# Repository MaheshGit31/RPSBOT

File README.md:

# RPSBOT

A rock-paper-scissors machine built with no microcontroller and, no firmware.

## Parts List

**4 BUTTONS**

**1. Clock — NE555 (U1)**

**2. Counter — CD4017 (U2)**

**3. Latches — 74HC02 NOR gates (U3, U4)**

**4. Comparator — 74HC08 AND + 74HC32 OR (U5–U9)**

(P = your pick, C = the computer's pick, r/p/s = rock/paper/scissors)

## Files

- `rps_logic.kicad_sch` / `rps_logic.kicad_pro` — schematic
- `rps_logic.kicad_pcb` — routed PCB 

## Images

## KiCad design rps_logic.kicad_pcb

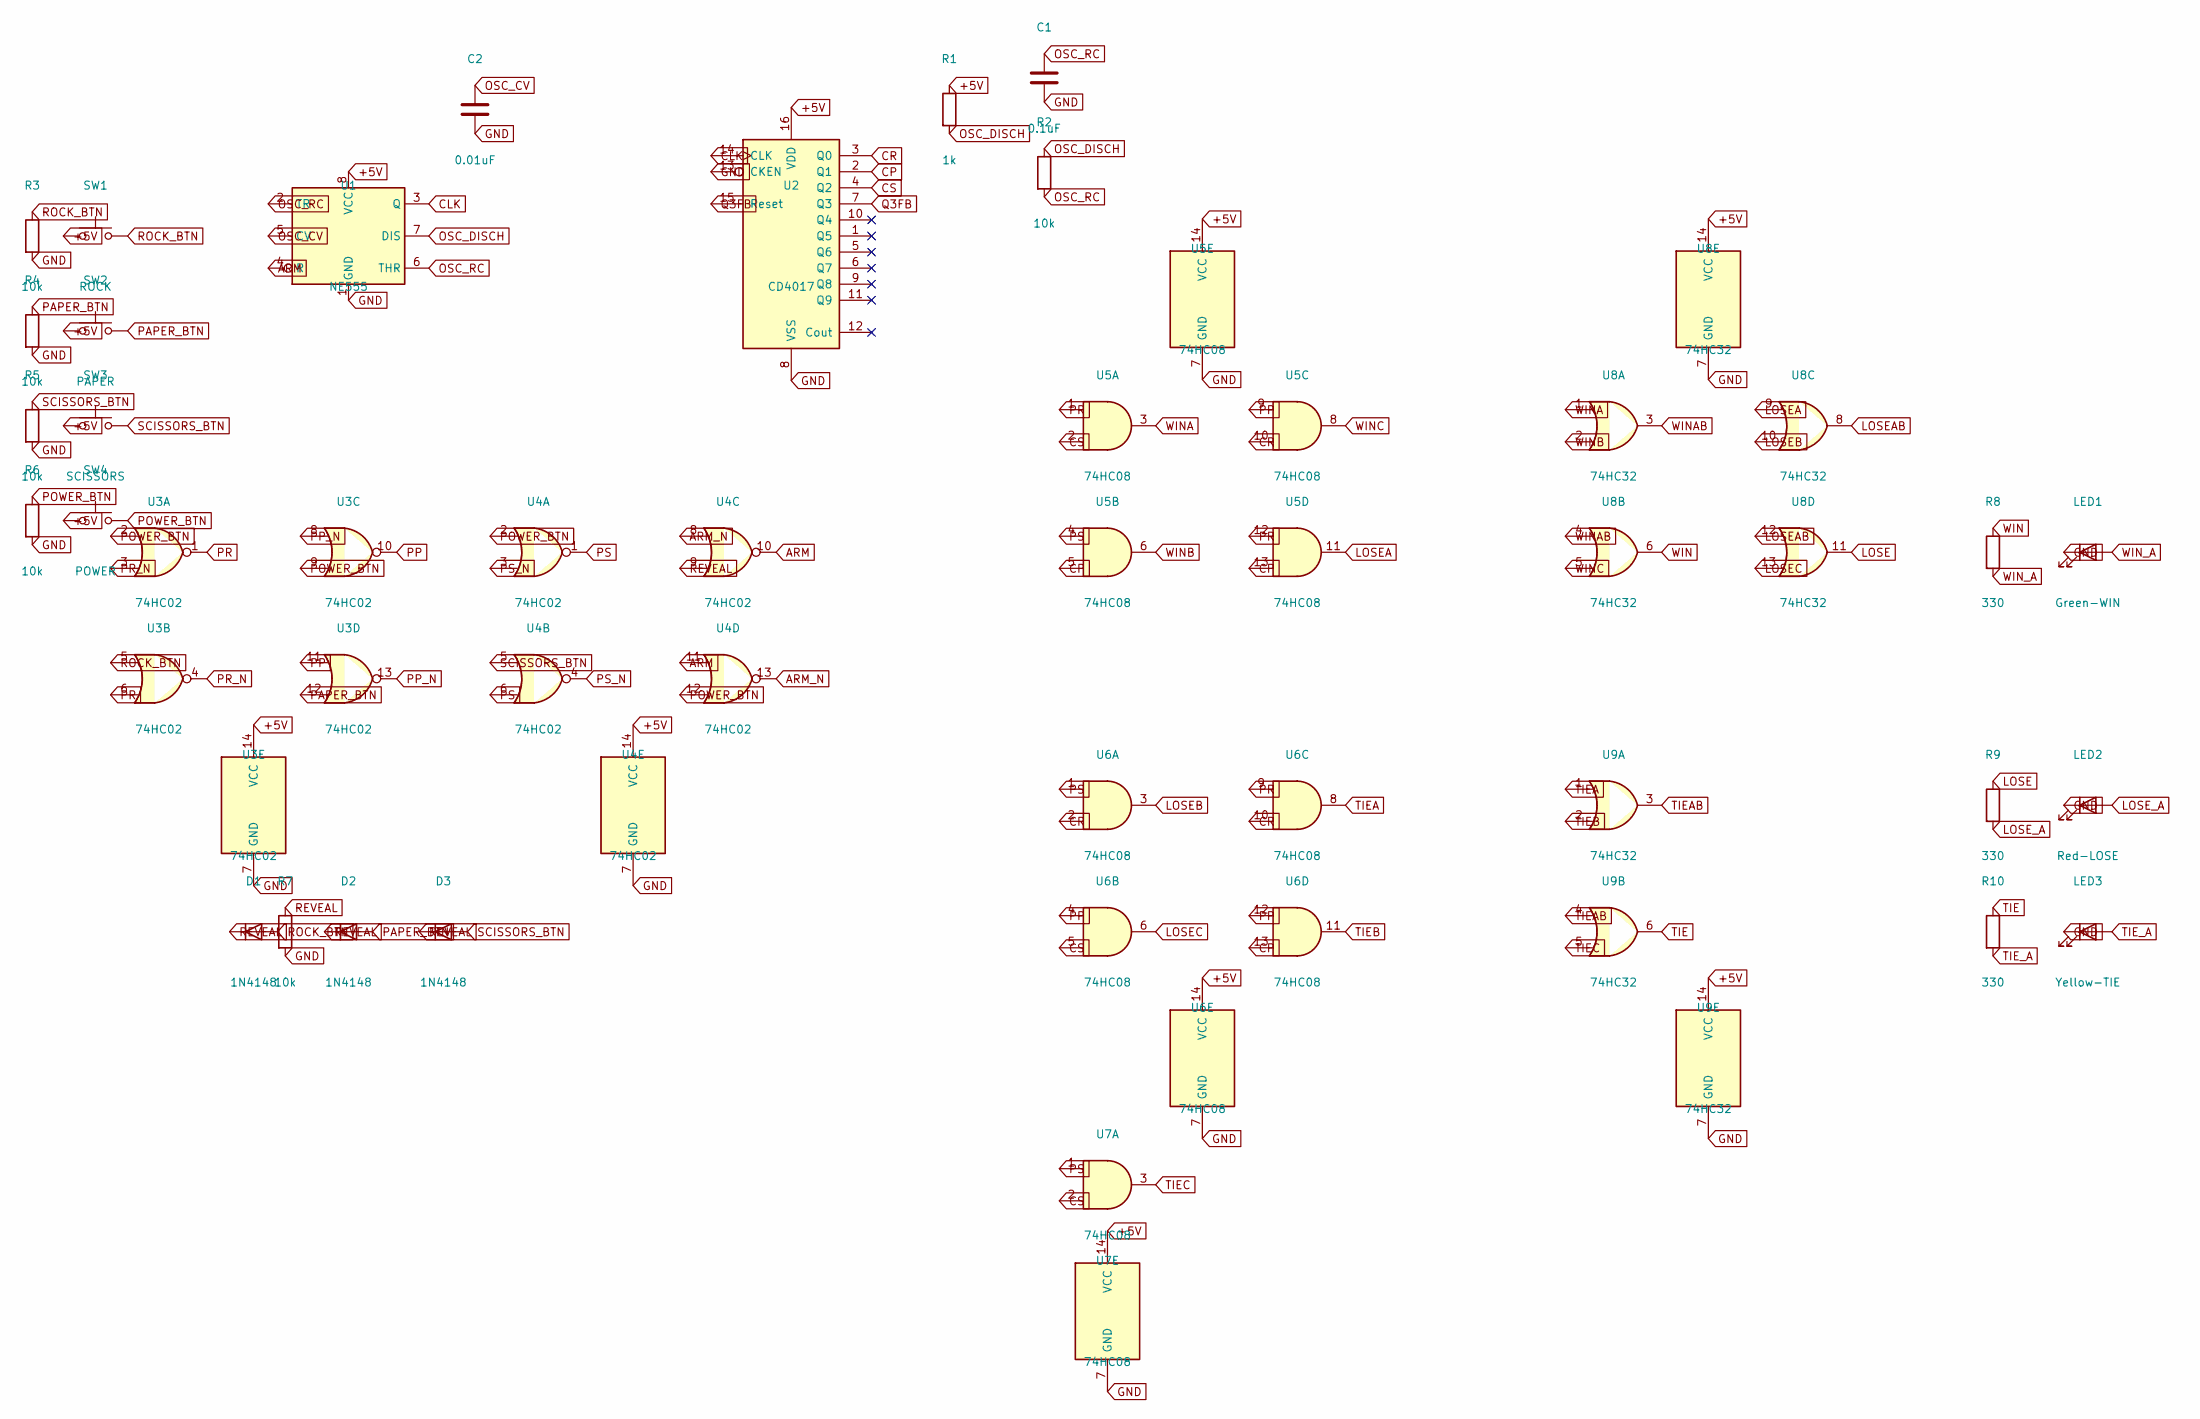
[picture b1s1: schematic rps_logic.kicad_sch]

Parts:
C1: 0.1uF; C_Disc_D3.0mm_W2.0mm_P2.50mm
C2: 0.01uF; C_Disc_D3.0mm_W2.0mm_P2.50mm
D1, D2, D3: 1N4148; D_DO-35_SOD27_P7.62mm_Horizontal
LED1: Green-WIN; LED_D5.0mm
LED2: Red-LOSE; LED_D5.0mm
LED3: Yellow-TIE; LED_D5.0mm
R1: 1k; R_Axial_DIN0207_L6.3mm_D2.5mm_P10.16mm_Horizontal
R2, R3, R4, R5, R6, R7: 10k; R_Axial_DIN0207_L6.3mm_D2.5mm_P10.16mm_Horizontal
R8, R9, R10: 330; R_Axial_DIN0207_L6.3mm_D2.5mm_P10.16mm_Horizontal
SW1: ROCK; SW_PUSH_6mm
SW2: PAPER; SW_PUSH_6mm
SW3: SCISSORS; SW_PUSH_6mm
SW4: POWER; SW_PUSH_6mm
U1: NE555; DIP-8_W7.62mm
U2: CD4017; DIP-16_W7.62mm
U3, U4: 74HC02; DIP-14_W7.62mm
U5, U6, U7: 74HC08; DIP-14_W7.62mm
U8, U9: 74HC32; DIP-14_W7.62mm

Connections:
+5V: R1.1, SW1.1, SW2.1, SW3.1, SW4.1, U1.8 (VCC), U2.16 (VDD), U3.14 (VCC), U4.14 (VCC), U5.14 (VCC), U6.14 (VCC), U7.14 (VCC), U8.14 (VCC), U9.14 (VCC)
ARM: U1.4 (R), U4.10, U4.11
ARM_N: U4.8, U4.13
CLK: U1.3 (Q), U2.14 (CLK)
CP: U2.2 (Q1), U5.5, U5.13, U6.13
CR: U2.3 (Q0), U5.10, U6.2, U6.10
CS: U2.4 (Q2), U5.2, U6.5, U7.2
GND: C1.2, C2.2, LED1.1 (K), LED2.1 (K), LED3.1 (K), R3.2, R4.2, R5.2, R6.2, R7.2, U1.1 (GND), U2.8 (VSS), U2.13 (CKEN), U3.7 (GND), U4.7 (GND), U5.7 (GND), U6.7 (GND), U7.7 (GND), U8.7 (GND), U9.7 (GND)
LOSE: R9.1, U8.11
LOSEA: U5.11, U8.9
LOSEAB: U8.8, U8.12
LOSEB: U6.3, U8.10
LOSEC: U6.6, U8.13
LOSE_A: LED2.2 (A), R9.2
OSC_CV: C2.1, U1.5 (CV)
OSC_DISCH: R1.2, R2.1, U1.7 (DIS)
OSC_RC: C1.1, R2.2, U1.2 (TR), U1.6 (THR)
PAPER_BTN: D2.2 (A), R4.1, SW2.2, U3.12
POWER_BTN: R6.1, SW4.2, U3.2, U3.9, U4.2, U4.12
PP: U3.10, U3.11, U5.9, U6.4, U6.12
PP_N: U3.8, U3.13
PR: U3.1, U3.6, U5.1, U5.12, U6.9
PR_N: U3.3, U3.4
PS: U4.1, U4.6, U5.4, U6.1, U7.1
PS_N: U4.3, U4.4
Q3FB: U2.7 (Q3), U2.15 (Reset)
REVEAL: D1.1 (K), D2.1 (K), D3.1 (K), R7.1, U4.9
ROCK_BTN: D1.2 (A), R3.1, SW1.2, U3.5
SCISSORS_BTN: D3.2 (A), R5.1, SW3.2, U4.5
TIE: R10.1, U9.6
TIEA: U6.8, U9.1
TIEAB: U9.3, U9.4
TIEB: U6.11, U9.2
TIEC: U7.3, U9.5
TIE_A: LED3.2 (A), R10.2
WIN: R8.1, U8.6
WINA: U5.3, U8.1
WINAB: U8.3, U8.4
WINB: U5.6, U8.2
WINC: U5.8, U8.5
WIN_A: LED1.2 (A), R8.2

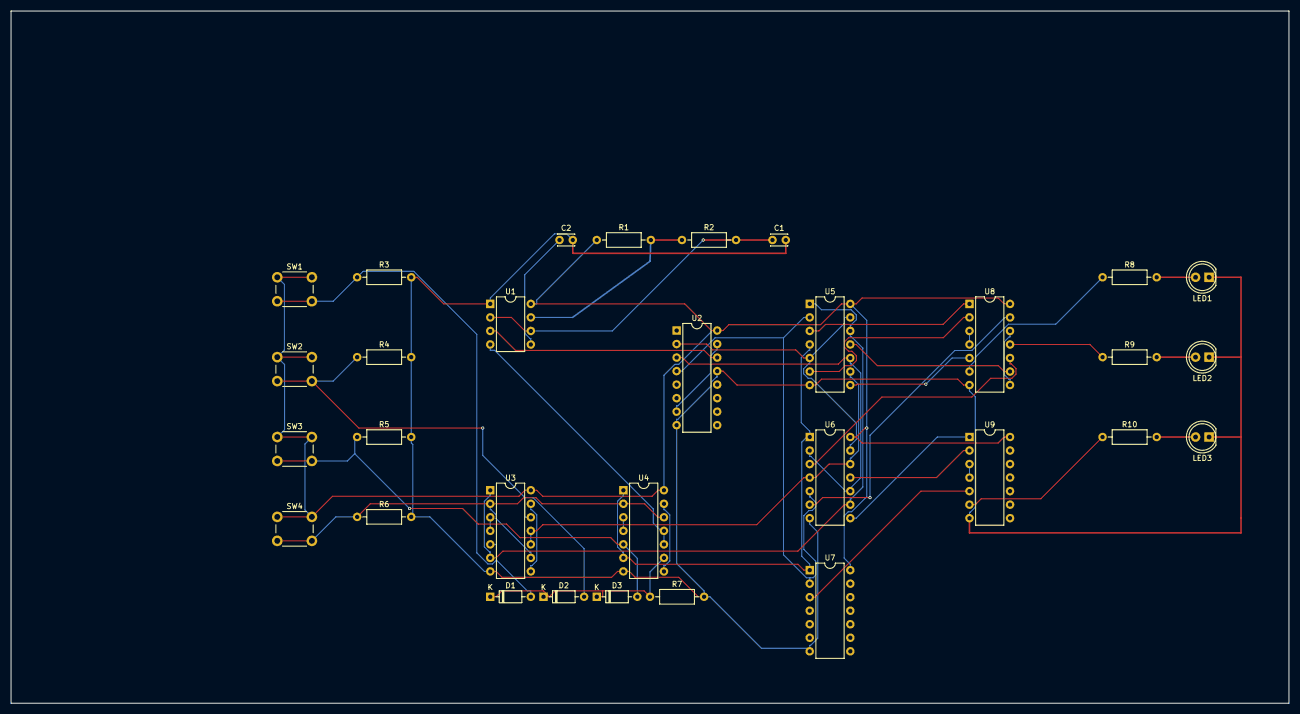
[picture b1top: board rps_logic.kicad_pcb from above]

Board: 2 copper layers, 240.0 x 130.0 mm, 31 parts (0 on the bottom side), 41 nets.
